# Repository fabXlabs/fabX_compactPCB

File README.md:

# fabX_compactPCB
Compact PCB (M5+CardReader+3xIO) for many simple Tasks

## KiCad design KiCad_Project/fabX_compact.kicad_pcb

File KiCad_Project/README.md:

# fabX_PCB

imported from gitlab
"Erweiterungsplatine für den m5 Stack zur Verwendung als Zugangssystem für Maschinen"

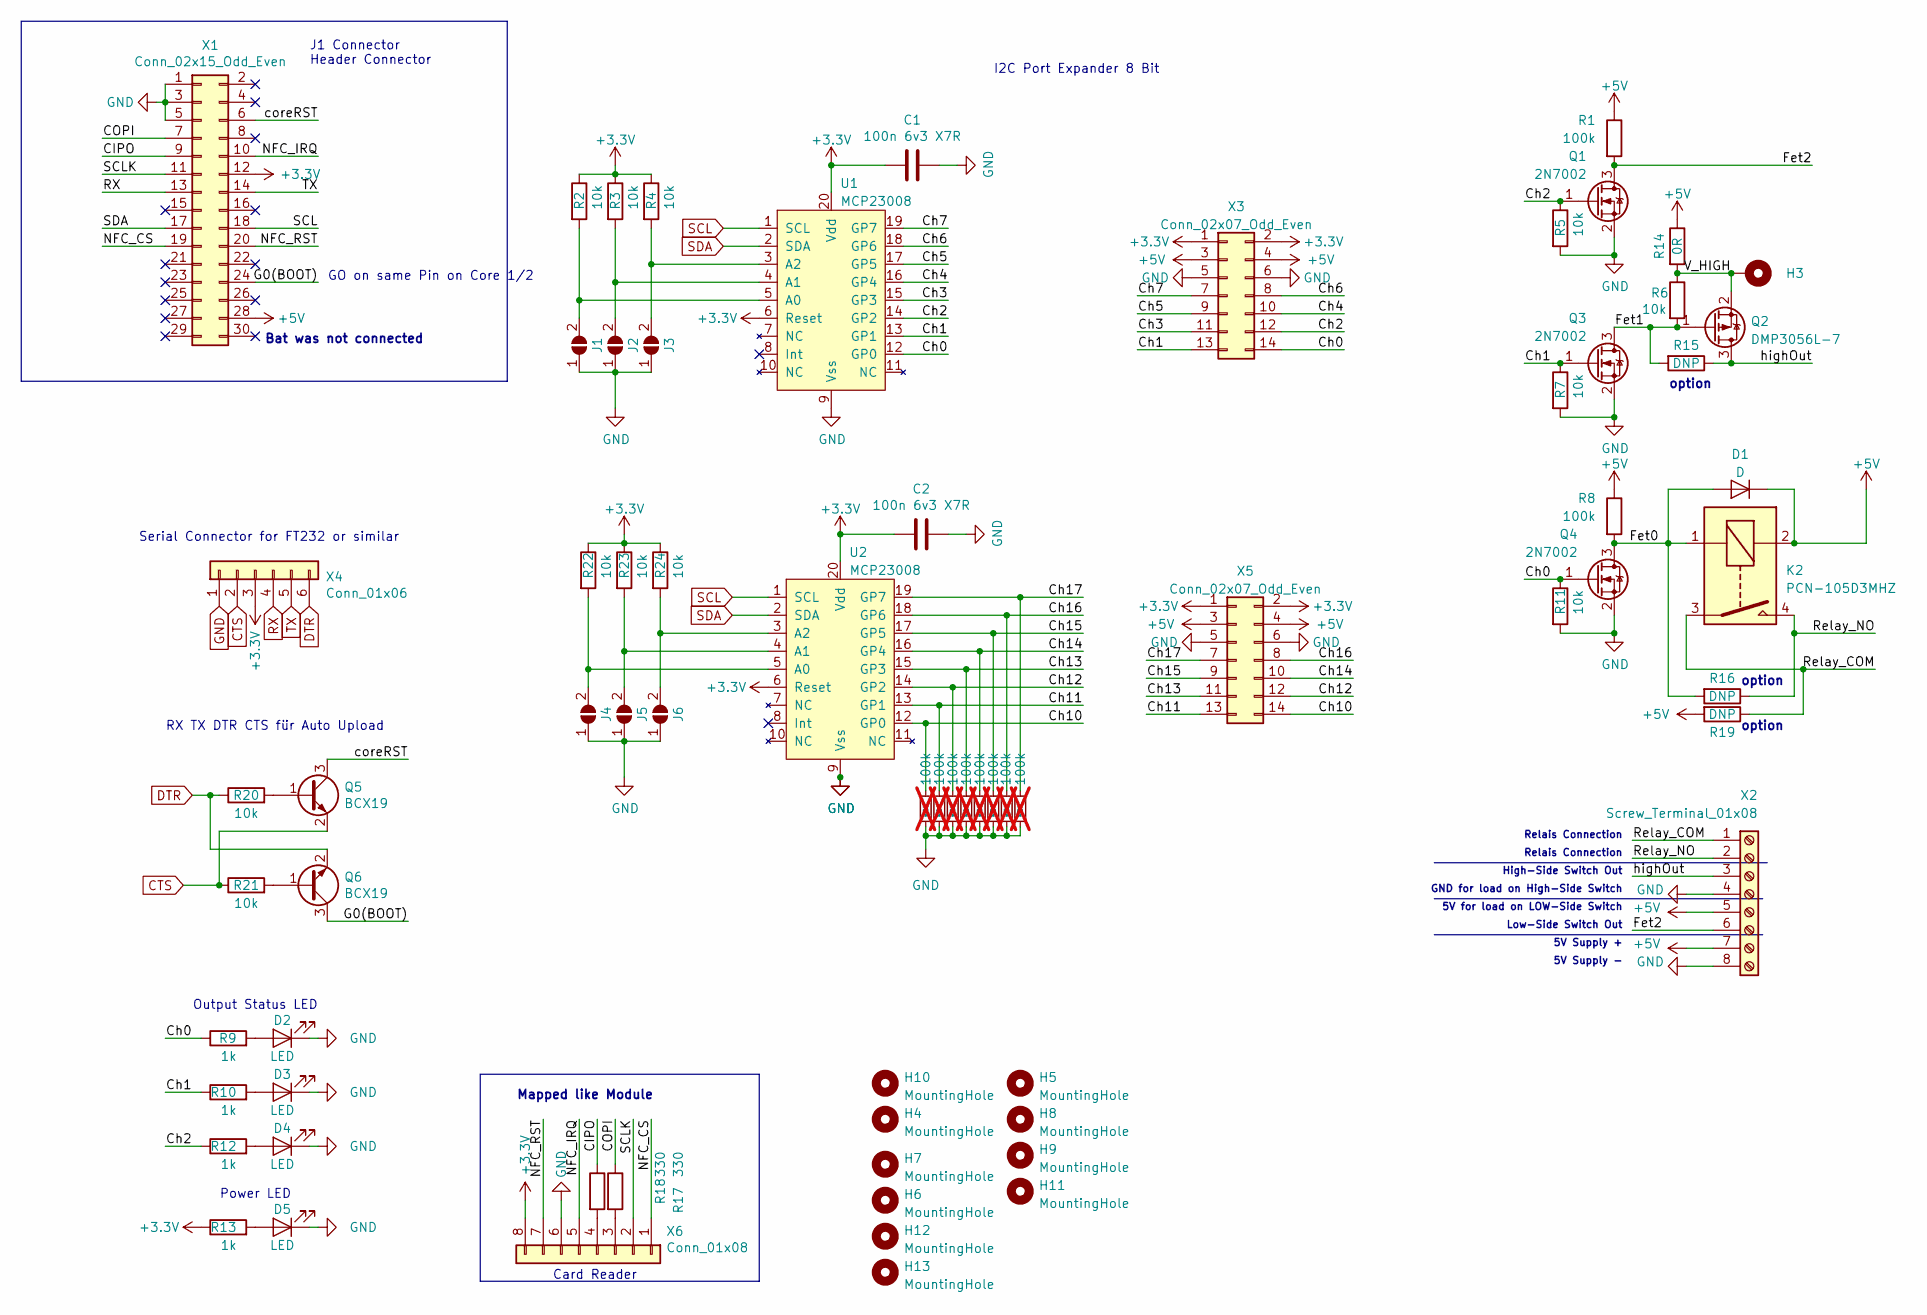
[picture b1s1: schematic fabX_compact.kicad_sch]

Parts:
C1, C2: 100n 6v3 X7R; C_0603_1608Metric; Farnell# 3345771
D1: D; D_; Farnell# 2760409
D2, D3, D4, D5: LED; LED_1206_3216Metric_ReverseMount_Hole1.8x2.4mm_3DMOD; Farnell# 2099257
H3: MountingHole_Pad; TestPoint_Loop_D2.50mm_Drill1.85mm
H4, H6, H7, H10, H12, H13: MountingHole; MountingHole_3.2mm_M3_noSolder
H5, H8, H9, H11: MountingHole; MountingHole_3.2mm_M3_noSolderCorner
J1, J2, J3, J4, J5, J6: SolderJumper_2_Open; SolderJumper-2_P1.3mm_Open_RoundedPad1.0x1.5mm
K2: PCN-105D3MHZ; Relay_SPST_TE_PCN-1xxD3MHZ; Farnell# 4444930
Q1, Q3, Q4: 2N7002; SOT-23; Farnell# 3924478
Q2: DMP3056L-7; SOT-23; Farnell# 3127362
Q5, Q6: BCX19; SOT-23; Farnell# 2317581
R1, R8: 100k; R_0603_1608Metric; Farnell# 3495222
R2, R3, R4, R5, R6, R7, R11, R20, R21, R22, R23, R24: 10k; R_0603_1608Metric; Farnell# 3495224
R9, R10, R12, R13: 1k; R_0603_1608Metric; Farnell# 3495238
R14: 0R; R_0603_1608Metric; Farnell# 2309106
R15: DNP; R_0603_1608Metric
R16, R19: DNP; R_2010_5025Metric
R17, R18: 330; R_0603_1608Metric; Farnell# 3950907
R25, R26, R27, R28, R29, R30, R31, R32: 100k; R_0603_1608Metric; not fitted
U1, U2: MCP23008; SSOP-20_5.3x7.2mm_P0.65mm; Farnell# 1605564
X1: Conn_02x15_Odd_Even; PinSocket_2x15_P2.54mm_Vertical
X2: Screw_Terminal_01x08; PhoenixContact_MSTBA_2,5_8-G-5,08_1x08_P5.08mm_Horizontal; Farnell# 2671266
X3, X5: Conn_02x07_Odd_Even; IDC-Header_2x07_P2.54mm_Horizontal; Farnell# 2356264
X4: Conn_01x06; PinSocket_1x06_P2.54mm_Horizontal; Farnell# 2084276
X6: Conn_01x08; PinSocket_1x08_P2.54mm_Vertical

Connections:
+3V3: C1.2, C2.2, R2.1, R3.1, R4.1, R13.1, R22.1, R23.1, R24.1, U1.6 (Reset), U1.20 (Vdd), U2.6 (Reset), U2.20 (Vdd), X1.12, X3.1, X3.2, X4.3, X5.1, X5.2, X6.8
+5V: D1.1 (K), K2.2, R1.1, R8.1, R14.1, R19.2, X1.28, X2.5, X2.7, X3.3, X3.4, X5.3, X5.4
/CIPO: R18.1, X1.9
/COPI: R17.1, X1.7
/Ch0: Q4.1 (G), R9.1, R11.1, U1.12 (GP0), X3.14
/Ch1: Q3.1 (G), R7.1, R10.1, U1.13 (GP1), X3.13
/Ch2: Q1.1 (G), R5.1, R12.1, U1.14 (GP2), X3.12
/Ch3: U1.15 (GP3), X3.11
/Ch4: U1.16 (GP4), X3.10
/Ch5: U1.17 (GP5), X3.9
/Ch6: U1.18 (GP6), X3.8
/Ch7: U1.19 (GP7), X3.7
/Ch10: R25.1, U2.12 (GP0), X5.14
/Ch11: R26.1, U2.13 (GP1), X5.13
/Ch12: R27.1, U2.14 (GP2), X5.12
/Ch13: R28.1, U2.15 (GP3), X5.11
/Ch14: R29.1, U2.16 (GP4), X5.10
/Ch15: R30.1, U2.17 (GP5), X5.9
/Ch16: R31.1, U2.18 (GP6), X5.8
/Ch17: R32.1, U2.19 (GP7), X5.7
/Fet0: D1.2 (A), K2.1, Q4.3 (D), R8.2, R16.2
/Fet1: Q2.1 (G), Q3.3 (D), R6.2, R15.2
/Fet2: Q1.3 (D), R1.2, X2.6
/G0(BOOT): Q6.3 (C), X1.24
/NFC_CS: X1.19, X6.1
/NFC_IRQ: X1.10, X6.5
/NFC_RST: X1.20, X6.7
/Relay_COM: K2.3, R19.1, X2.1
/Relay_NO: K2.4, R16.1, X2.2
/SCLK: X1.11, X6.2
/V_HIGH: H3.1, Q2.2 (S), R6.1, R14.2
/coreRST: Q5.3 (C), X1.6
/highOut: Q2.3 (D), R15.1, X2.3
CTS: Q5.2 (E), R21.1, X4.2
DTR: Q6.2 (E), R20.1, X4.6
GND: C1.1, C2.1, D2.1 (K), D3.1 (K), D4.1 (K), D5.1 (K), J1.1 (A), J2.1 (A), J3.1 (A), J4.1 (A), J5.1 (A), J6.1 (A), Q1.2 (S), Q3.2 (S), Q4.2 (S), R5.2, R7.2, R11.2, R25.2, R26.2, R27.2, R28.2, R29.2, R30.2, R31.2, R32.2, U1.9 (Vss), U2.9 (Vss), X1.1, X1.3, X1.5, X2.4, X2.8, X3.5, X3.6, X4.1, X5.5, X5.6, X6.6
unnamed: D2.2 (A), R9.2
unnamed: D3.2 (A), R10.2
unnamed: D4.2 (A), R12.2
unnamed: D5.2 (A), R13.2
unnamed: J1.2 (B), R2.2, U1.5 (A0)
unnamed: J2.2 (B), R3.2, U1.4 (A1)
unnamed: J3.2 (B), R4.2, U1.3 (A2)
unnamed: J4.2 (B), R22.2, U2.5 (A0)
unnamed: J5.2 (B), R23.2, U2.4 (A1)
unnamed: J6.2 (B), R24.2, U2.3 (A2)
unnamed: Q5.1 (B), R20.2
unnamed: Q6.1 (B), R21.2
unnamed: R17.2, X6.3
unnamed: R18.2, X6.4
RX: X1.13, X4.4
SCL: U1.1 (SCL), U2.1 (SCL), X1.18
SDA: U1.2 (SDA), U2.2 (SDA), X1.17
TX: X1.14, X4.5

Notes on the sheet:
Card Reader
GND for load on High-Side Switch
GO on same Pin on Core 1/2
Relais Connection
High-Side Switch Out
RX TX DTR CTS für Auto Upload
option
5V Supply -
Low-Side Switch Out
Bat was not connected
5V Supply +
Serial Connector for FT232 or similar
J1 Connector Header Connector
Output Status LED
Mapped like Module
5V for load on LOW-Side Switch
I2C Port Expander 8 Bit
Power LED

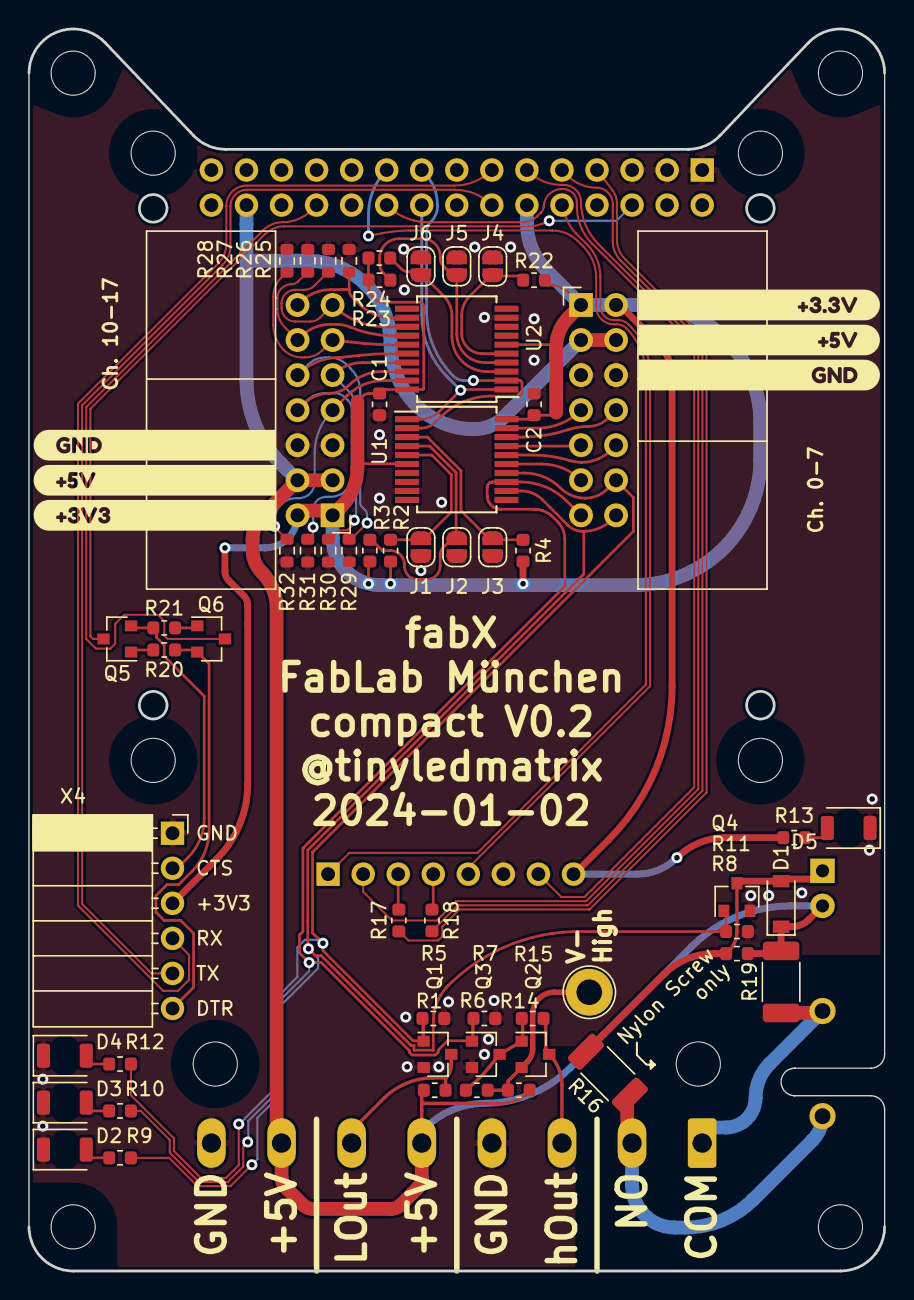
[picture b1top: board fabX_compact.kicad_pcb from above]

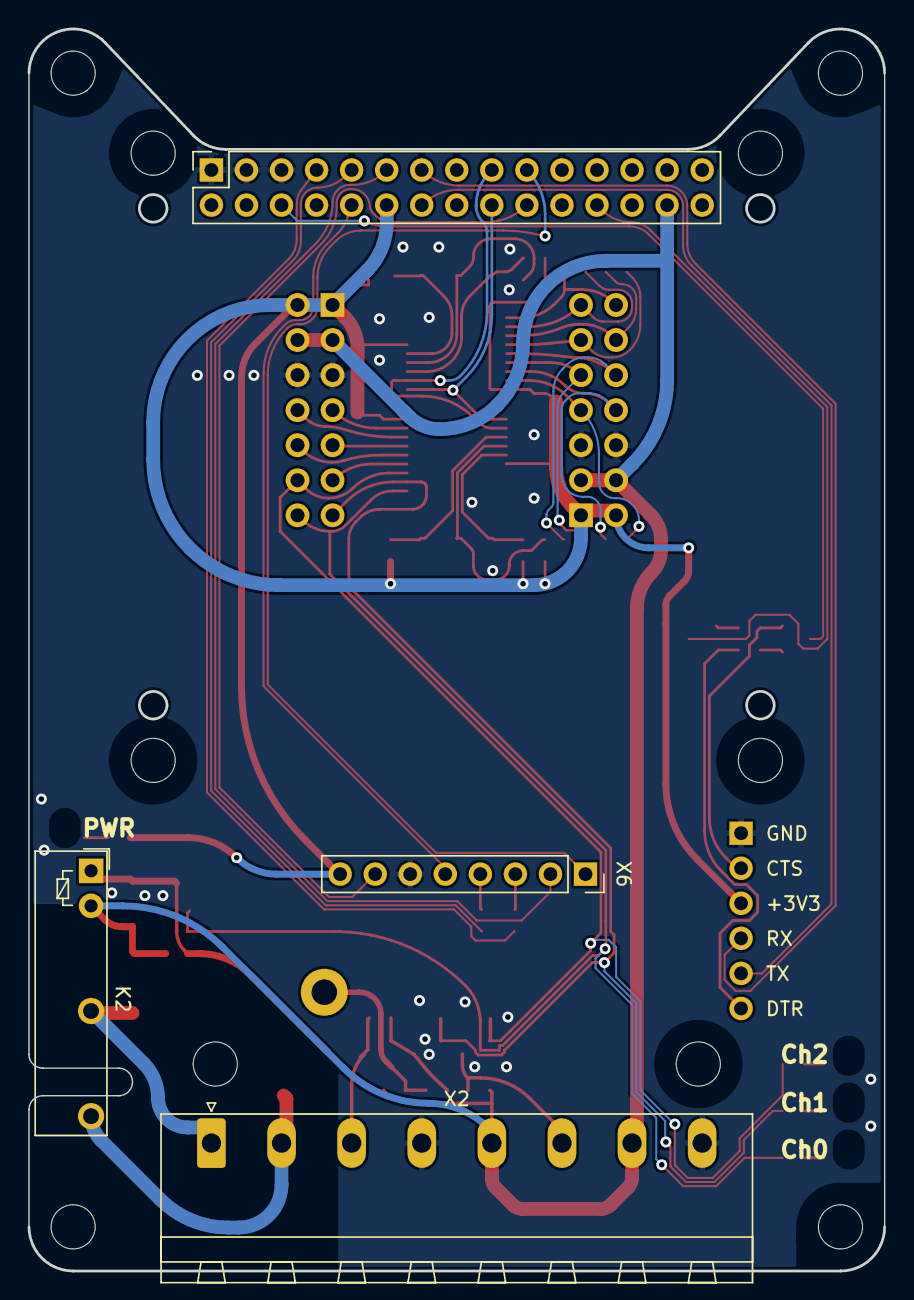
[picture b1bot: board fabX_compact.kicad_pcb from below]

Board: 2 copper layers, 62.0 x 90.0 mm, 77 parts (4 on the bottom side), 54 nets.

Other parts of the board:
kibuzzard-632A457B: G***; kibuzzard-632A457B
kibuzzard-632A4549: G***; kibuzzard-632A4549
kibuzzard-632A4565: G***; kibuzzard-632A4565
kibuzzard-635FD36E: G***; kibuzzard-635FD36E
kibuzzard-635FD364: G***; kibuzzard-635FD364
kibuzzard-635FD378: G***; kibuzzard-635FD378

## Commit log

2022-09-20 Initial kicad Push
    Still much TODO but could get seen by a second pair of eyes
2022-09-20 Added some MCAD Screenshots for assembly/case idea
2022-09-26 some PCB progress
2022-09-29 minor desktop sync
2022-10-31 PCB progress
2022-10-31 added bom
2022-11-14 minor gitignore edit
2023-02-13 iBOM
2023-02-20 change license
2023-12-29 add pulldowns for inputs
2024-01-02 new PCB Version V0.2
    Added new Pulddown Rs to PCB
    DRC okay
